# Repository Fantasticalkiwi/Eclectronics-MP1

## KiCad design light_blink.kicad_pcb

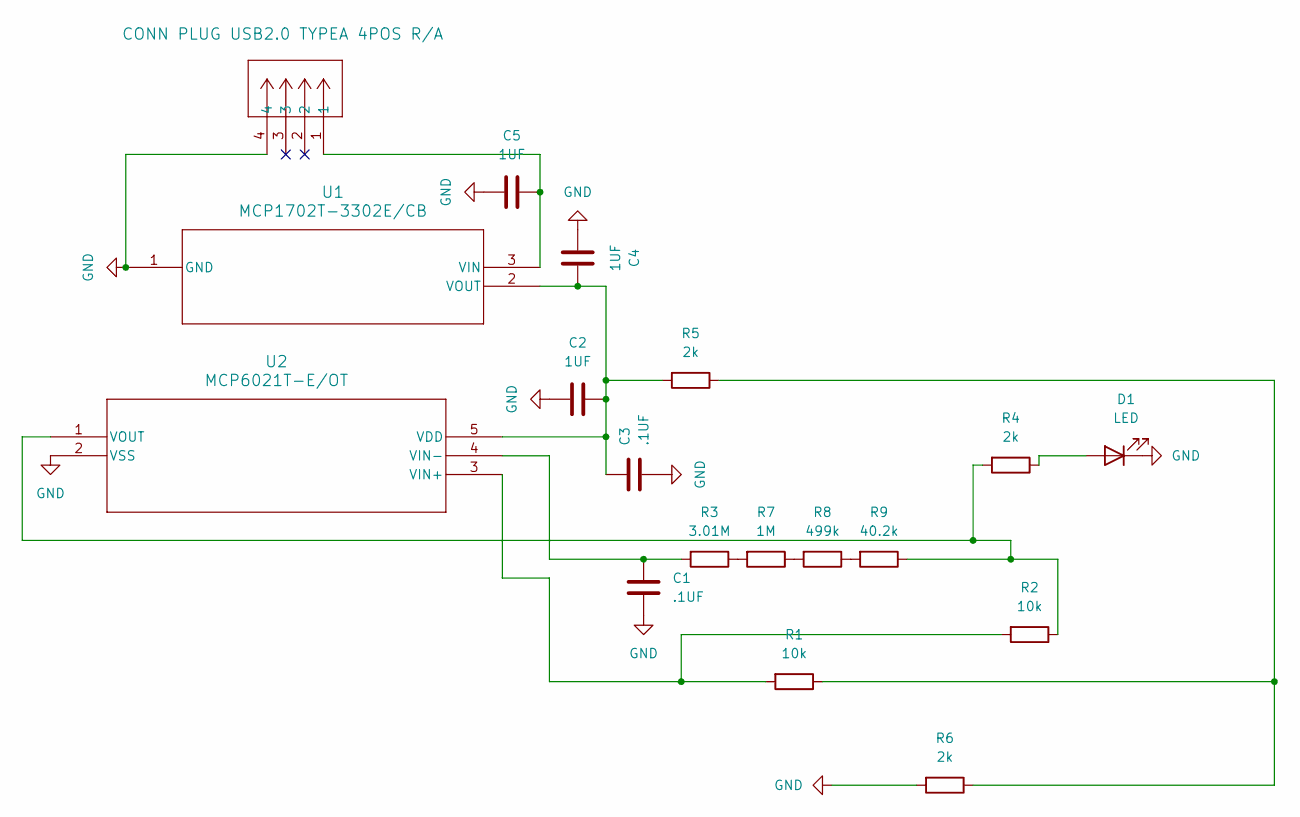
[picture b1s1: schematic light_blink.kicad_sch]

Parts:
C1, C3: .1UF; C_0603_1608Metric
C2, C4, C5: 1UF; C_0603_1608Metric
D1: LED; LED_LTST-C171_LTO
J1: CONN PLUG USB2.0 TYPEA 4POS R/A; CONN_480370001_MOL
R1, R2: 10k; R_0603_1608Metric
R3: 3.01M; R_0603_1608Metric
R4, R5, R6: 2k; R_0603_1608Metric
R7: 1M; R_0603_1608Metric
R8: 499k; R_0603_1608Metric
R9: 40.2k; R_0603_1608Metric
U1: MCP1702T-3302E/CB; SOT-23A_MC_MCH
U2: MCP6021T-E/OT; SOT-23-5_MC_MCH

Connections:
GND: C1.2, C2.2, C3.2, C4.2, C5.2, D1.1 (K), J1.4, R6.2, U1.1 (GND), U2.2 (VSS)
unnamed: D1.2 (A), R4.1
unnamed: R1.1, R5.1, R6.1
unnamed: R3.1, R7.2
unnamed: R7.1, R8.2
unnamed: R8.1, R9.2
unnamed: C5.1, J1.1, U1.3 (VIN)
unnamed: C2.1, C3.1, C4.1, R5.2, U1.2 (VOUT), U2.5 (VDD)
unnamed: R1.2, R2.2, U2.3 (VIN+)
unnamed: C1.1, R3.2, U2.4 (VIN-)
unnamed: R2.1, R4.2, R9.1, U2.1 (VOUT)

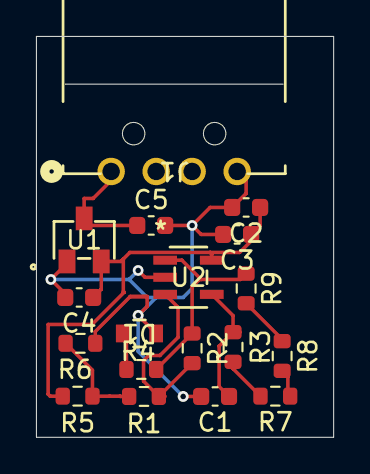
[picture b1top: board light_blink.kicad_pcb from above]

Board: 2 copper layers, 16.5 x 22.3 mm, 18 parts (0 on the bottom side), 11 nets.
